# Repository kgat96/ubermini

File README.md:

# ubermini

Project Ubermini is an open source wireless development platform suitable for Bluetooth experimentation. Ubermini ships with a capable BLE (Bluetooth Smart) sniffer and can sniff some data from Basic Rate (BR) Bluetooth Classic connections.

clone [Ubertooth](https://github.com/greatscottgadgets/ubertooth) project

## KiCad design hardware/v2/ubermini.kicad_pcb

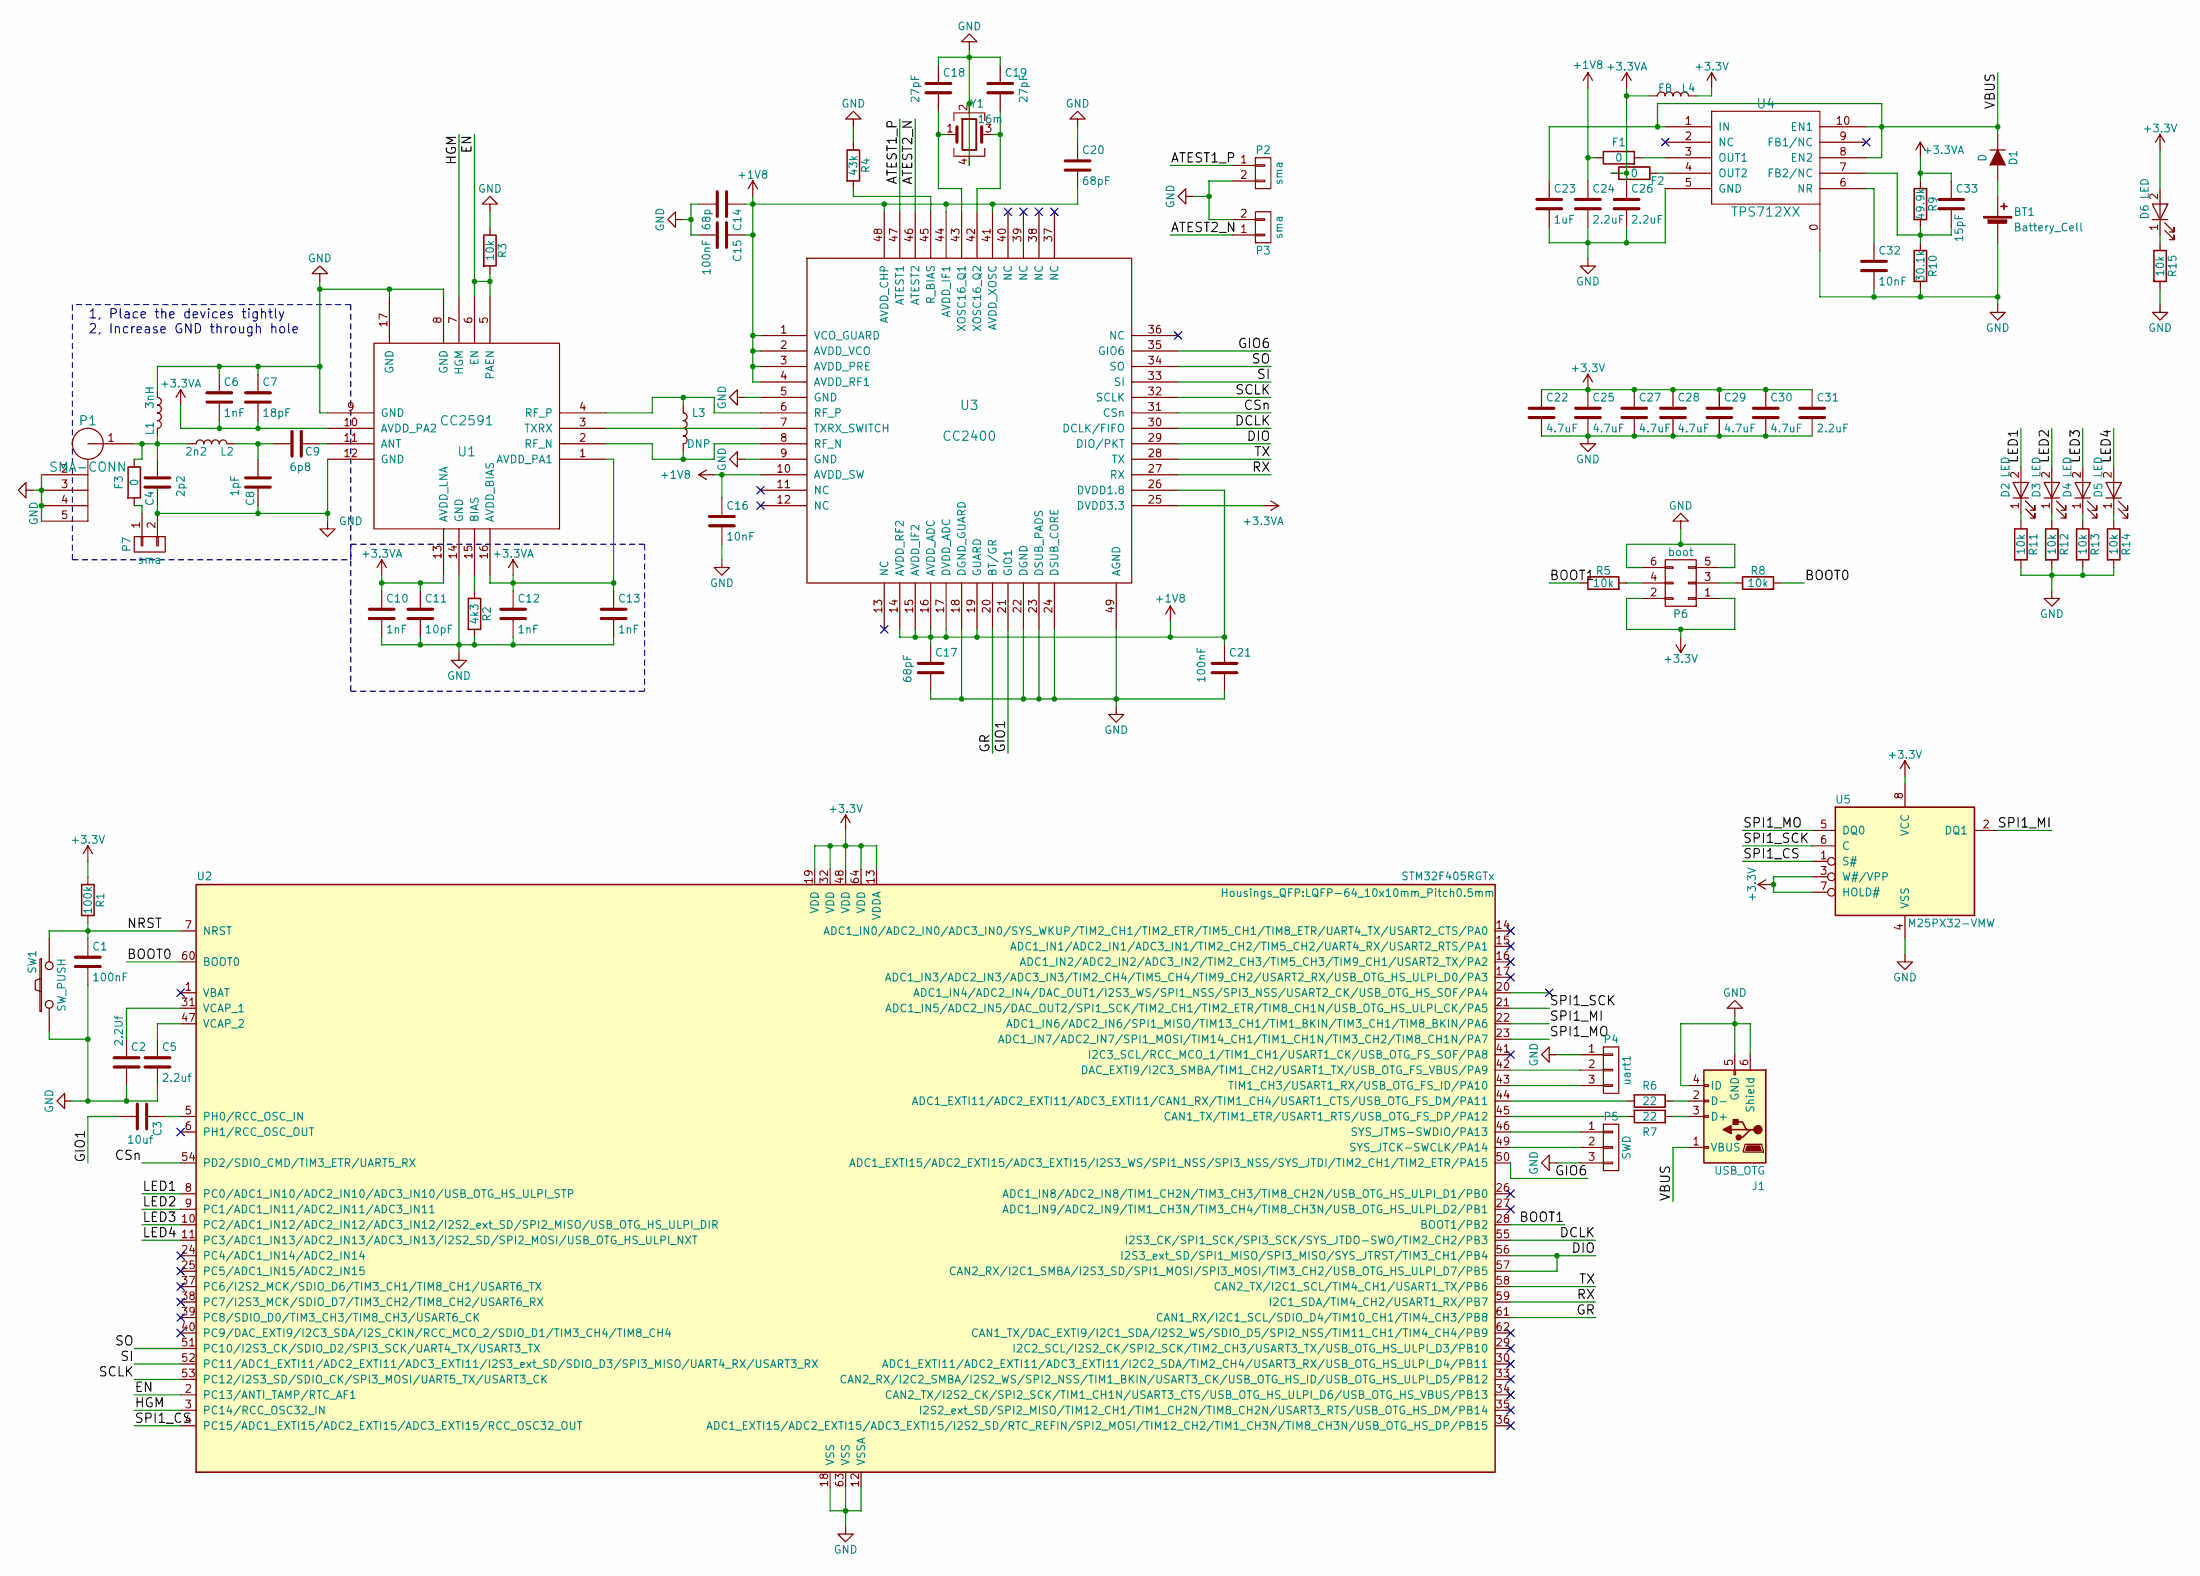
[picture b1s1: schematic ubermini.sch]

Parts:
BT1: Battery_Cell; Pin_Header_Straight_1x02
C1, C15, C21: 100nF; C_0603_HandSoldering
C2: 2.2Uf; C_0603_HandSoldering
C3: 10uf; C_0603_HandSoldering
C4: 2p2; C_0402
C5: 2.2uf; C_0603_HandSoldering
C6, C10, C12, C13: 1nF; C_0603_HandSoldering
C7: 18pF; C_0603_HandSoldering
C8: 1pF; C_0402
C9: 6p8; C_0402
C11: 10pF; C_0603_HandSoldering
C14: 68p; C_0603_HandSoldering
C16, C32: 10nF; C_0603_HandSoldering
C17, C20: 68pF; C_0603_HandSoldering
C18, C19: 27pF; C_0603_HandSoldering
C22, C25, C27, C28, C29, C30: 4.7uF; C_0603_HandSoldering
C23: 1uF; C_0603_HandSoldering
C24, C26, C31: 2.2uF; C_0603_HandSoldering
C33: 15pF; C_0603_HandSoldering
D1: D; R_0805_HandSoldering
D2, D3, D4, D5, D6: LED; LED_0805
F1, F2, F3: 0; C_0201
J1: USB_OTG; USB_Mini-B_s
L1: 3nH; C_0603
L2: 2n2; C_0603
L3: DNP; C_0402
L4: FB; C_0603_HandSoldering
P1: SMA-CONN; sma
P2, P3, P7: sma; U.FL
P4: uart1; Pin_Header_Straight_1x03
P5: SWD; Pin_Header_Straight_1x03
P6: boot; Pin_Header_Straight_2x03
R1: 100k; R_0603_HandSoldering
R2: 4k3; R_0603_HandSoldering
R3, R5, R8, R11, R12, R13, R14, R15: 10k; R_0603_HandSoldering
R4: 43k; R_0603_HandSoldering
R6, R7: 22; R_0603_HandSoldering
R9: 49.9k; R_0603_HandSoldering
R10: 30.1k; R_0603_HandSoldering
SW1: SW_PUSH; SW_SPST_FSMSM
U1: CC2591; cc2591
U2: STM32F405RGTx; LQFP-64_10x10mm_Pitch0.5mm
U3: CC2400; cc2400
U4: TPS712XX; tps712
U5: M25PX32-VMW; winband_spi_flash
Y1: 16m; 3225

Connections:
+1V8: C14.1, C15.1, C16.1, C17.1, C20.2, C21.1, C24.1, F1.1, U3.1 (VCO_GUARD), U3.2 (AVDD_VCO), U3.3 (AVDD_PRE), U3.4 (AVDD_RF1), U3.10 (AVDD_SW), U3.14 (AVDD_RF2), U3.15 (AVDD_IF2), U3.16 (AVDD_ADC), U3.17 (DVDD_ADC), U3.19 (GUARD), U3.26 (DVDD1.8), U3.41 (AVDD_XOSC), U3.44 (AVDD_IF1), U3.48 (AVDD_CHP)
+3.3VA: C6.2, C7.2, C10.1, C11.1, C12.1, C13.1, C26.1, C33.1, F2.1, L4.1, R9.1, U1.1 (AVDD_PA1), U1.10 (AVDD_PA2), U1.13 (AVDD_LNA), U1.16 (AVDD_BIAS), U3.25 (DVDD3.3)
+3V3: C22.1, C25.1, C27.1, C28.1, C29.1, C30.1, C31.1, D6.2 (A), L4.2, P6.1, P6.2, R1.1, U2.13 (VDDA), U2.19 (VDD), U2.32 (VDD), U2.48 (VDD), U2.64 (VDD), U5.3 (W#/VPP), U5.7 (HOLD#), U5.8 (VCC)
/ATEST1_P: P2.1, U3.47 (ATEST1)
/ATEST2_N: P3.1, U3.46 (ATEST2)
/BOOT0: R8.2, U2.60 (BOOT0)
/BOOT1: R5.1, U2.28 (BOOT1/PB2)
/CSn: U2.54 (PD2/SDIO_CMD/TIM3_ETR/UART5_RX), U3.31 (CSn)
/DCLK: U2.55 (I2S3_CK/SPI1_SCK/SPI3_SCK/SYS_JTDO-SWO/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), U3.30 (DCLK/FIFO)
/DIO: U2.56 (I2S3_ext_SD/SPI1_MISO/SPI3_MISO/SYS_JTR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), U2.57 (CAN2_RX/I2C1_SMBA/I2S3_SD/SPI1_MOSI/SPI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), U3.29 (DIO/PKT)
/EN: R3.2, U1.5 (PAEN), U1.6 (EN), U2.2 (PC13/ANTI_TAMP/RTC_AF1)
/GIO1: C3.2, U3.21 (GIO1)
/GIO6: U2.50 (ADC1_EXTI15/ADC2_EXTI15/ADC3_EXTI15/I2S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), U3.35 (GIO6)
/GR: U2.61 (CAN1_RX/I2C1_SCL/SDIO_D4/TIM10_CH1/TIM4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), U3.20 (BT/GR)
/HGM: U1.7 (HGM), U2.3 (PC14/RCC_OSC32_IN)
/LED1: D2.2 (A), U2.8 (PC0/ADC1_IN10/ADC2_IN10/ADC3_IN10/USB_O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)
/LED2: D3.2 (A), U2.9 (PC1/ADC1_IN11/ADC2_IN11/ADC3_IN11)
/LED3: D4.2 (A), U2.10 (PC2/ADC1_IN12/ADC2_IN12/ADC3_IN12/I2S2_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)
/LED4: D5.2 (A), U2.11 (PC3/ADC1_IN13/ADC2_IN13/ADC3_IN13/I2S2_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)
/NRST: C1.1, R1.2, SW1.2, U2.7 (NRST)
/RX: U2.59 (I2C1_SDA/TIM4_CH2/USART1_RX/PB7), U3.27 (RX)
/SCLK: U2.53 (PC12/I2S3_SD/SDIO_CK/SPI3_MOSI/UART5_TX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), U3.32 (SCLK)
/SI: U2.52 (PC11/ADC1_EXTI11/ADC2_EXTI11/ADC3_EXTI1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), U3.33 (SI)
/SO: U2.51 (PC10/I2S3_CK/SDIO_D2/SPI3_SCK/UART4_TX/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), U3.34 (SO)
/SPI1_CS: U2.4 (PC15/ADC1_EXTI15/ADC2_EXTI15/ADC3_EXTI1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), U5.1 (S#)
/SPI1_MI: U2.22 (ADC1_IN6/ADC2_IN6/SPI1_MISO/TIM13_CH1/T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), U5.2 (DQ1)
/SPI1_MO: U2.23 (ADC1_IN7/ADC2_IN7/SPI1_MOSI/TIM14_CH1/T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), U5.5 (DQ0)
/SPI1_SCK: U2.21 (ADC1_IN5/ADC2_IN5/DAC_OUT2/SPI1_SCK/TIM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), U5.6 (C)
/TX: U2.58 (CAN2_TX/I2C1_SCL/TIM4_CH1/USART1_TX/PB6), U3.28 (TX)
/VBUS: C23.1, D1.1 (K), J1.1 (VBUS), U4.1 (IN), U4.8 (EN2), U4.10 (EN1)
GND: BT1.2 (-), C1.2, C2.2, C4.1, C5.2, C6.1, C7.1, C8.1, C10.2, C11.2, C12.2, C13.2, C14.2, C15.2, C16.2, C17.2, C18.1, C19.1, C20.1, C21.2, C22.2, C23.2, C24.2, C25.2, C26.2, C27.2, C28.2, C29.2, C30.2, C31.2, C32.2, J1.4 (ID), J1.5 (GND), J1.6 (Shield), L1.1, P1.2 (GND), P1.3 (GND), P1.4 (GND), P1.5 (GND), P2.2, P3.2, P4.1, P5.3, P6.5, P6.6, P7.2, R2.2, R3.1, R4.1, R10.2, R11.2, R12.2, R13.2, R14.2, R15.2, SW1.1, U1.8 (GND), U1.9 (GND), U1.12 (GND), U1.14 (GND), U1.17 (GND), U2.12 (VSSA), U2.18 (VSS), U2.63 (VSS), U3.5 (GND), U3.9 (GND), U3.18 (DGND_GUARD), U3.22 (DGND), U3.23 (DSUB_PADS), U3.24 (DSUB_CORE), U3.49 (AGND), U4.0, U4.5 (GND), U5.4 (VSS), Y1.2, Y1.4
unnamed: BT1.1 (+), D1.2 (A)
unnamed: C2.1, U2.31 (VCAP_1)
unnamed: C3.1, U2.5 (PH0/RCC_OSC_IN)
unnamed: C4.2, F3.1, L1.2, L2.1, P1.1 (RF)
unnamed: C5.1, U2.47 (VCAP_2)
unnamed: C8.2, C9.2, L2.2
unnamed: C9.1, U1.11 (ANT)
unnamed: C18.2, U3.43 (XOSC16_Q1), Y1.1
unnamed: C19.2, U3.42 (XOSC16_Q2), Y1.3
unnamed: C32.1, U4.6 (NR)
unnamed: C33.2, R9.2, R10.1, U4.7 (FB2/NC)
unnamed: D2.1 (K), R11.1
unnamed: D3.1 (K), R12.1
unnamed: D4.1 (K), R13.1
unnamed: D5.1 (K), R14.1
unnamed: D6.1 (K), R15.1
unnamed: F1.2, U4.3 (OUT1)
unnamed: F2.2, U4.4 (OUT2)
unnamed: F3.2, P7.1
unnamed: J1.2 (D-), R6.1
unnamed: J1.3 (D+), R7.1
unnamed: L3.1, U1.4 (RF_P), U3.6 (RF_P)
unnamed: L3.2, U1.2 (RF_N), U3.8 (RF_N)
unnamed: P4.2, U2.42 (DAC_EXTI9/I2C3_SMBA/TIM1_CH2/USART1_TX/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)
unnamed: P4.3, U2.43 (TIM1_CH3/USART1_RX/USB_OTG_FS_ID/PA10)
unnamed: P5.1, U2.46 (SYS_JTMS-SWDIO/PA13)
unnamed: P5.2, U2.49 (SYS_JTCK-SWCLK/PA14)
unnamed: P6.3, R8.1
unnamed: P6.4, R5.2
unnamed: R2.1, U1.15 (BIAS)
unnamed: R4.2, U3.45 (R_BIAS)
unnamed: R6.2, U2.44 (ADC1_EXTI11/ADC2_EXTI11/ADC3_EXTI11/CAN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)
unnamed: R7.2, U2.45 (CAN1_TX/TIM1_ETR/USART1_RTS/USB_OTG_FS_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)
unnamed: U1.3 (TXRX), U3.7 (TXRX_SWITCH)

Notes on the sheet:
1, Place the devices tightly 2, Increase GND through hole

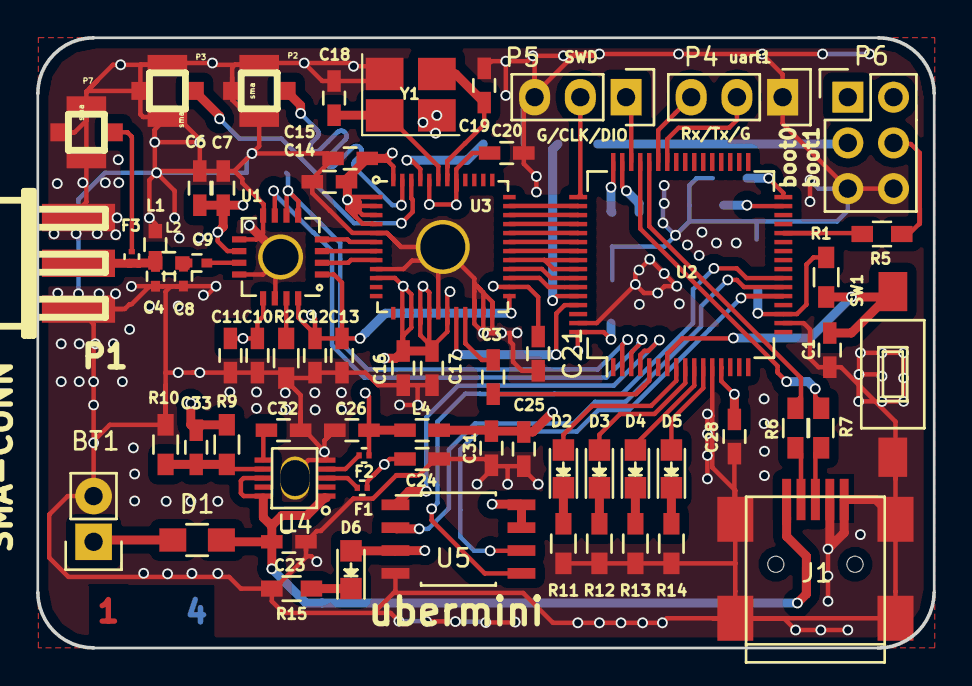
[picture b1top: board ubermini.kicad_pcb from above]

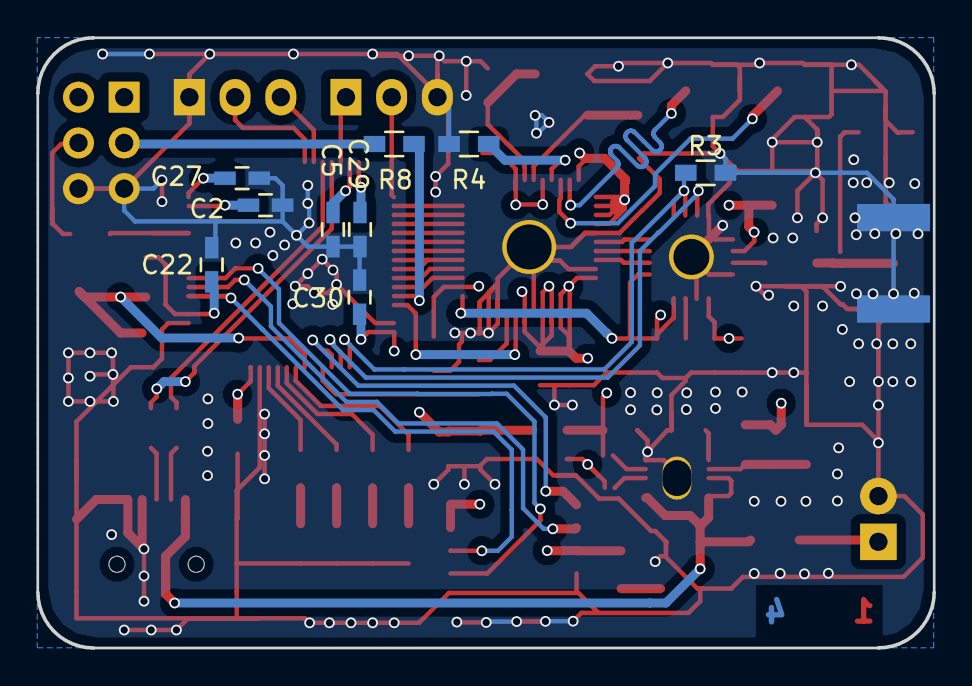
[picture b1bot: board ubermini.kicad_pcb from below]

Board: 4 copper layers, 49.8 x 33.9 mm, 76 parts (9 on the bottom side), 65 nets.

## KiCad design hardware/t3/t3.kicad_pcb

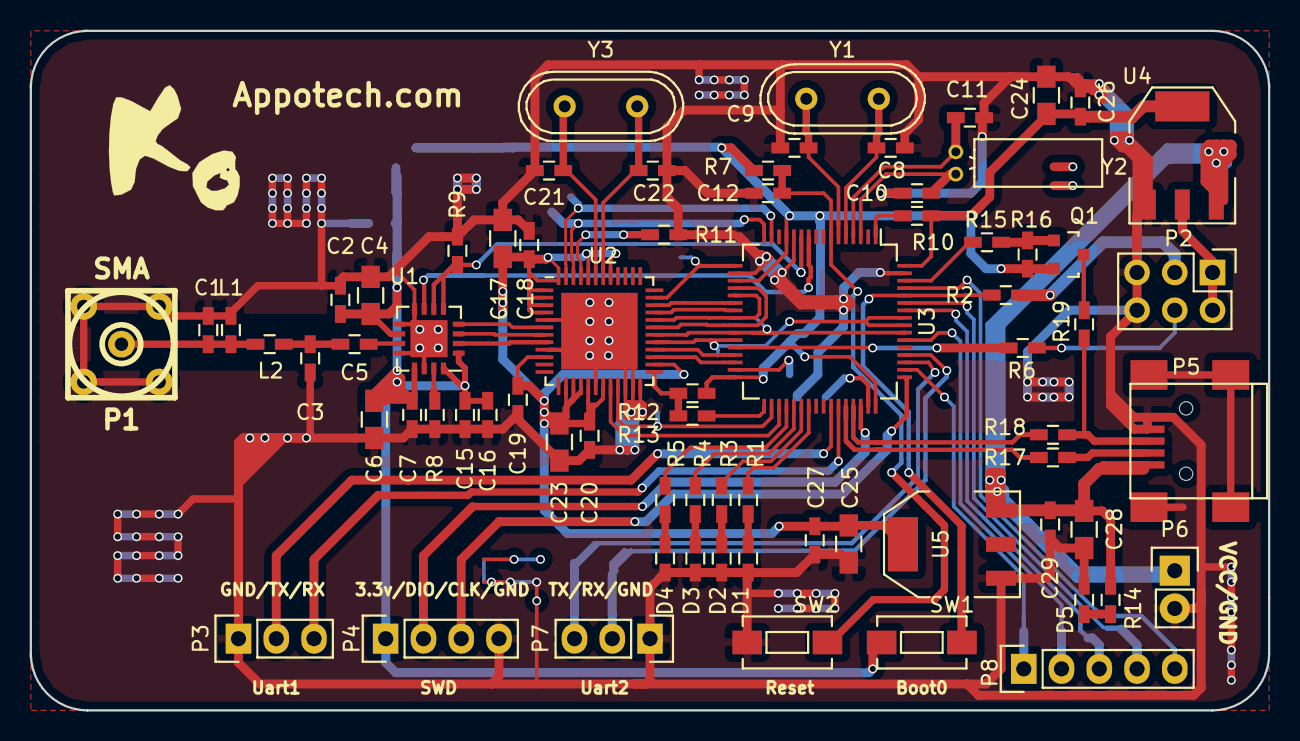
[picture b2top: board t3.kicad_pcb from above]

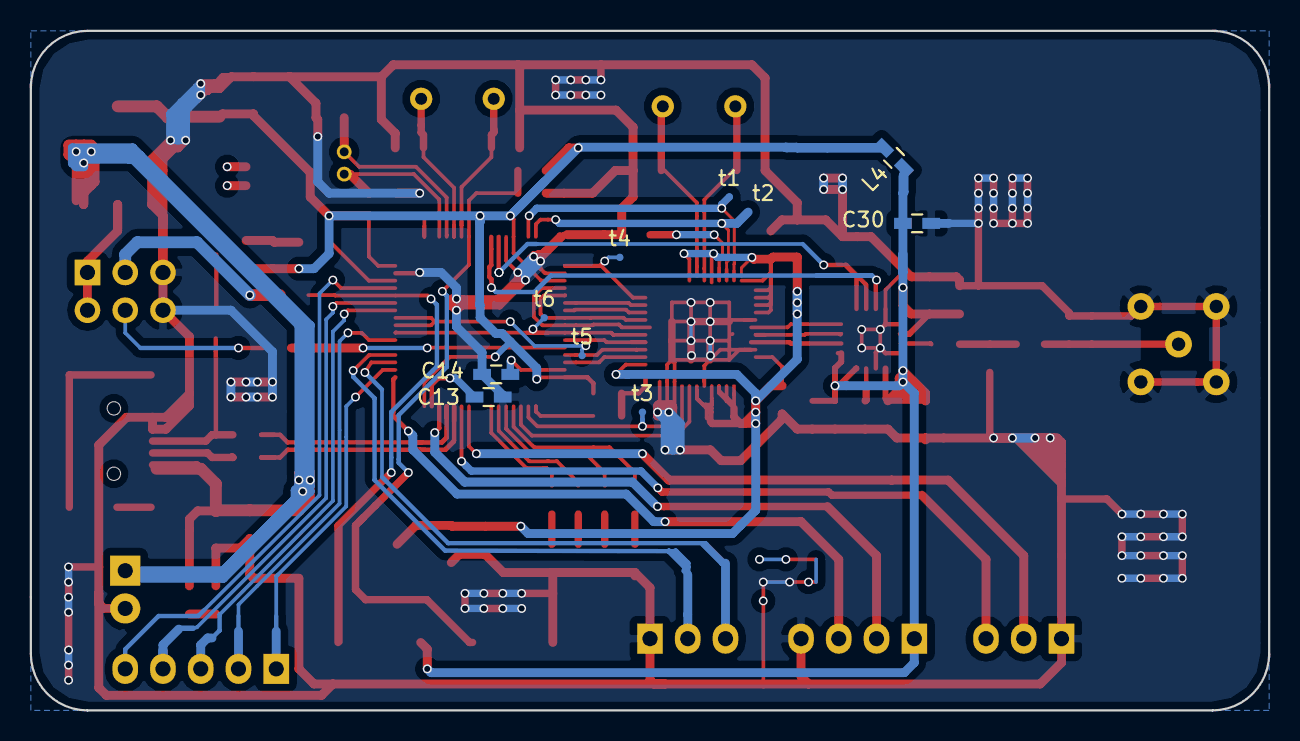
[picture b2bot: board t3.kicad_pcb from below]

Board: 2 copper layers, 83.3 x 45.7 mm, 82 parts (10 on the bottom side), 71 nets.

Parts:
C1: 2p2; C_0603_HandSoldering
C2: 18pf; C_0603_HandSoldering
C3: 1pf; C_0603_HandSoldering
C4, C6: 1nf; C_0805_HandSoldering
C5: 6p8; C_0603_HandSoldering
C7: 10pf; C_0603_HandSoldering
C8, C9: 22pf; C_0603_HandSoldering
C10, C11: 6pf; C_0603_HandSoldering
C12, C26, C27, C29: 100nf; C_0603_HandSoldering
C13, C14: 2.2uf; C_0603_HandSoldering
C15, C16: 1nf; C_0603_HandSoldering
C17, C23: 100nf; C_0805_HandSoldering
C18, C20: 68pf; C_0603_HandSoldering
C19: 10nf; C_0603_HandSoldering
C21, C22: 27pf; C_0603_HandSoldering
C24, C25, C28: 10uf; C_0805_HandSoldering
C30: 2.2pf; C_0603_HandSoldering
D1, D2, D3, D4, D5: LED; C_0603_HandSoldering
L1: 3nH; C_0603_HandSoldering
L2: 2n2; C_0603_HandSoldering
L4: 1Kohms; C_0603_HandSoldering
P1: SMA; lemo_epb00250ntn
P2: CON; Pin_Header_Straight_2x03
P3: UART1; Pin_Header_Straight_1x03
P4: SWD; Pin_Header_Straight_1x04
P5: USB_B; USB_Mini-B
P6: power; Pin_Header_Straight_1x02
P7: UART2; Pin_Header_Straight_1x03
P8: Debug; Pin_Header_Straight_1x05
Q1: 9012; SOT-23
R1, R3, R4, R5, R14: 330; C_0603_HandSoldering
R2, R6: 10K; C_0603_HandSoldering
R7: 100K; C_0603_HandSoldering
R8: 4k3; C_0603_HandSoldering
R9, R16: 10k; C_0603_HandSoldering
R10, R13: 0R; C_0603_HandSoldering
R11: 43k; C_0603_HandSoldering
R12: 0R(NC); C_0603_HandSoldering
R15: 2k2; C_0603_HandSoldering
R17, R18: 22R; C_0603_HandSoldering
R19: 1K5; C_0603_HandSoldering
SW1, SW2: SW_PUSH; SW_SPST_EVQPE1
U1: CC2591; QFN-16-1EP_4x4mm_Pitch0.65mm
U2: CC2400; cc2400_Soldering
U3: STM32F405RGTx; LQFP-64_10x10mm_Pitch0.5mm
U4: LM1117-3.3; SOT-223
U5: LM1117-1.8; SOT-223
Y1, Y3: 16MHz; Crystal_HC49-U_Vertical
Y2: 32.768k; Crystal_Round_Horizontal_3mm
t1, t2, t3, t4, t5, t6: TST; test_pin

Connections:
+1V8: C17.1, C18.1, C19.1, C20.1, C23.1, C25.2, C27.2, U2.1, U2.2, U2.3, U2.4, U2.10, U2.14, U2.15, U2.16, U2.17, U2.19, U2.26, U2.41, U2.44, U2.48, U5.2, U5.4
+3.3VADC: C2.2, C4.2, C6.1, C7.1, C15.1, C16.1, C30.1, L4.1, P4.1, SW1.1, U1.1, U1.10, U1.13, U1.16
+3V3: C24.1, C26.1, L4.2, P2.1, P2.2, Q1.2, R7.1, R10.2, R12.2, R16.2, U3.13, U3.19, U3.32, U3.48, U3.64, U4.2, U4.4
/ATEST1: U2.47, U3.15, t1.1
/ATEST2: U2.46, U3.16, t2.1
/BOOT0: R2.2, SW1.2, U3.60
/BOOT1: R6.1, U3.28
/CSn: U2.31, U3.20, U3.25
/DCLK: U2.30, U3.26, U3.55, t6.1
/DIO: U2.29, U3.27, U3.56, U3.57, t5.1
/GIO1: U2.21, U3.34, t3.1
/GIO6: U2.35, U3.17, t4.1
/GPIO3.3: R13.1, U3.33
/GR: U2.20, U3.35
/HGM: U1.7, U3.10
/LED1: R1.1, U3.39
/LED2: R3.1, U3.38
/LED3: R4.1, U3.37
/LED4: R5.1, U3.36
/NRST: C12.1, R7.2, SW2.2, U3.7
/PAEN: R9.1, U1.5, U1.6, U3.11
/RX: U2.27, U3.30
/SCLK: U2.32, U3.21, U3.24
/SI: U2.33, U3.23
/SO: U2.34, U3.22
/TX: U2.28, U3.29
/UAER1_RX: P3.3, U3.43
/UAER1_TX: P3.2, U3.42
/UAER2_RX: P7.2, U3.52
/UAER2_TX: P7.3, U3.51
/USBEN: R15.2, U3.62
/VBUS: C28.2, C29.2, P5.1, P6.1, R14.1, U4.3, U5.3
/debug1: P8.3, U3.58
/debug2: P8.4, U3.59
/debug3: P8.5, U3.61
/debug4: P8.1, U3.50
/debug5: P8.2, U3.54
GND: C1.1, C2.1, C3.1, C4.1, C6.2, C7.2, C8.2, C9.2, C10.2, C11.2, C12.2, C13.2, C14.2, C15.2, C16.2, C17.2, C18.2, C19.2, C20.2, C21.2, C22.2, C23.2, C24.2, C25.1, C26.2, C27.1, C28.1, C29.1, C30.2, D1.1, D2.1, D3.1, D4.1, D5.1, L1.1, P1.2, P2.5, P2.6, P3.1, P4.4, P5.4, P5.5, P6.2, P7.1, R8.2, R9.2, R11.2, SW2.1, U1.8, U1.9, U1.12, U1.14, U1.17, U2.5, U2.9, U2.18, U2.22, U2.23, U2.24, U2.49, U3.12, U3.18, U3.63, U4.1, U5.1
unnamed: C1.2, L1.2, L2.1, P1.1
unnamed: C3.2, C5.2, L2.2
unnamed: C5.1, U1.11
unnamed: C8.1, U3.5, Y1.2
unnamed: C9.1, U3.6, Y1.1
unnamed: C10.1, U3.3, Y2.2
unnamed: C11.1, U3.4, Y2.1
unnamed: C13.1, U3.31
unnamed: C14.1, U3.47
unnamed: C21.1, U2.43, Y3.1
unnamed: C22.1, U2.42, Y3.2
unnamed: D1.2, R1.2
unnamed: D2.2, R3.2
unnamed: D3.2, R4.2
unnamed: D4.2, R5.2
unnamed: D5.2, R14.2
unnamed: U1.4, U2.6
unnamed: U1.2, U2.8
unnamed: P2.3, R2.1
unnamed: P2.4, R6.2
unnamed: P4.2, U3.46
unnamed: P4.3, U3.49
unnamed: P5.2, R17.2
unnamed: P5.3, R18.2, R19.1
unnamed: Q1.1, R15.1, R16.1
unnamed: Q1.3, R19.2
unnamed: R8.1, U1.15
unnamed: R10.1, U3.1
unnamed: R11.1, U2.45
unnamed: R12.1, R13.2, U2.25
unnamed: R17.1, U3.44
unnamed: R18.1, U3.45
unnamed: U1.3, U2.7

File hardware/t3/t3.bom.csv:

Reference, Value, Footprint, Datasheet

U3,STM32F405RGTx,Housings_QFP:LQFP-64_10x10mm_Pitch0.5mm,
U2,CC2400,Housings_DFN_QFN:QFN-48-1EP_7x7mm_Pitch0.5mm,
U1,CC2591,Housings_DFN_QFN:QFN-16-1EP_4x4mm_Pitch0.65mm,

*U4,LM1117-3.3,TO_SOT_Packages_SMD:SOT-223,
*U5,LM1117-1.8,TO_SOT_Packages_SMD:SOT-223,

*Y1,16MHz,Crystals:Crystal_HC49-U_Vertical,
*Y2,32.768k,Crystals:Crystal_Round_Horizontal_3mm,

*Q1,9012,TO_SOT_Packages_SMD:SOT-23,
*D1,D2,D3,D4,D5,LED,Capacitors_SMD:C_0603_HandSoldering,


*R8,			4.3k,Capacitors_SMD:C_0603_HandSoldering,
*R11,		43k,Capacitors_SMD:C_0603_HandSoldering,
*R17,R18,	22R,Capacitors_SMD:C_0603_HandSoldering,
*R19,		1.5K,Capacitors_SMD:C_0603_HandSoldering,
*R15,		2.2k,Capacitors_SMD:C_0603_HandSoldering,
*R2,R6,R9,R16,		10k,Capacitors_SMD:C_0603_HandSoldering,
*R7,			100K,Capacitors_SMD:C_0603_HandSoldering,
*R1,R3,R4,R5,R14,	330,Capacitors_SMD:C_0603_HandSoldering,

*R10,		0R,Capacitors_SMD:C_0603_HandSoldering,



*C1,C30,  		2.2pf,Capacitors_SMD:C_0603_HandSoldering,
*C14,C13,		2.2uf,Capacitors_SMD:C_0603_HandSoldering,
*C9,C8,			22pf,Capacitors_SMD:C_0603_HandSoldering,
*C2,			18pf,Capacitors_SMD:C_0603_HandSoldering,

*C17,C23,C12,C29,C26,C27,	100nf,Capacitors_SMD:C_0805_HandSoldering,
*C19,			10nf,Capacitors_SMD:C_0603_HandSoldering,
*C3,				1pf,Capacitors_SMD:C_0603_HandSoldering,
*C16,C15,C6,C4,	1nf,Capacitors_SMD:C_0603_HandSoldering,
*C7,				10pf,Capacitors_SMD:C_0603_HandSoldering,

*C5,				6.8pf,Capacitors_SMD:C_0603_HandSoldering,
*C18,C20,		68pf,Capacitors_SMD:C_0603_HandSoldering,
*C21,C22,		27pf,Capacitors_SMD:C_0603_HandSoldering,
*C11,C10,		6pf,Capacitors_SMD:C_0603_HandSoldering,
*C28,C24,C25,	10uf,Capacitors_SMD:C_0805_HandSoldering,

*** Lx,1.5nH, 1nH 0402
*** L2,2.2nH,Capacitors_SMD:C_0603_HandSoldering,
*** L1,3nH,Capacitors_SMD:C_0603_HandSoldering,
*L4,1Kohms,Capacitors_SMD:C_0603_HandSoldering,

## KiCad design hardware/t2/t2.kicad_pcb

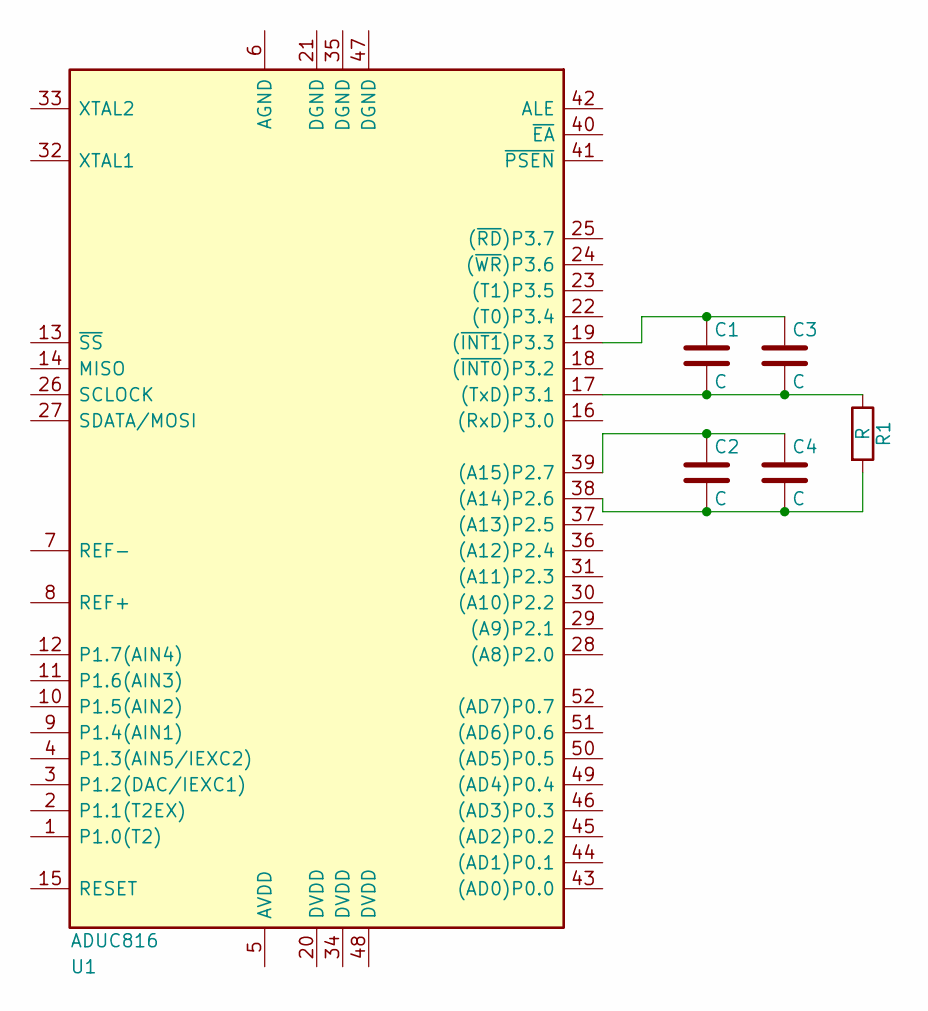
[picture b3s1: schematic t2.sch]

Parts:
C1, C2: C; C_0402
C3, C4: C; C_0603
R1: R; C_0603
U1: ADUC816; LQFP-52_10x10mm_Pitch0.65mm

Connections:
unnamed: C1.1, C3.1, U1.19 ((~INT1~)P3.3)
unnamed: C1.2, C3.2, R1.1, U1.17 ((TxD)P3.1)
unnamed: C2.1, C4.1, U1.39 ((A15)P2.7)
unnamed: C2.2, C4.2, R1.2, U1.38 ((A14)P2.6)

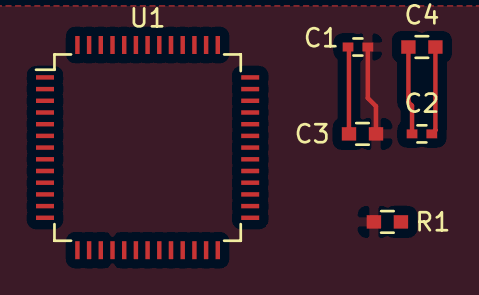
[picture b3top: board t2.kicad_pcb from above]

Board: 2 copper layers, 6 parts (0 on the bottom side), 4 nets.

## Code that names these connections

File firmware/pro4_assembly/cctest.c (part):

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
#define PIN_MOSI    GPIO7       /* Pa.7  */
#define PIN_MISO    GPIO6       /* Pa.6  */
#define PIN_GIO6    GPIO3       /* Pa.3  */

#define PIN_ATEST1  GPIO1       /* Pa.1  */
#define PIN_ATEST2  GPIO2       /* Pa.2  */

#define PIN_CC3V3   GPIO12      /* Pb.12 */
#define PIN_RX      GPIO11      /* Pb.11 */
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#define PIN_USRLED  GPIO8       /* Pc.8  */
#define PIN_RXLED   GPIO7       /* Pc.7  */
#define PIN_TXLED   GPIO6       /* Pc.6  */
#define PIN_CSN     GPIO5       /* Pc.5  */
#define PIN_SCLK    GPIO4       /* Pc.4  */
#define PIN_PAEN    GPIO3       /* Pc.3  */
#define PIN_HGM     GPIO2       /* Pc.2  */

//#define USRLED     (FIO1PIN & PIN_USRLED)
#define USRLED_SET gpio_set(GPIOC, PIN_USRLED)
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#define RX_CLR     gpio_clear(GPIOB, PIN_RX)
#define TX_SET     gpio_set(GPIOB, PIN_TX)
#define TX_CLR     gpio_clear(GPIOB, PIN_TX)
#define CSN_SET    gpio_set(GPIOC, PIN_CSN)
#define CSN_CLR    gpio_clear(GPIOC, PIN_CSN)
#define SCLK_SET   gpio_set(GPIOC, PIN_SCLK)
#define SCLK_CLR   gpio_clear(GPIOC, PIN_SCLK)
#define MOSI_SET   gpio_set(GPIOA, PIN_MOSI)
#define MOSI_CLR   gpio_clear(GPIOA, PIN_MOSI)
//#define GIO6       (FIO2PIN & PIN_GIO6)
#define GIO6_SET   gpio_set(GPIOA, PIN_GIO6)
#define GIO6_CLR   gpio_clear(GPIOA, PIN_GIO6)
#define BTGR_SET   gpio_set(GPIOB, PIN_BTGR)
#define BTGR_CLR   gpio_clear(GPIOB, PIN_BTGR)
#define MISO       gpio_get(GPIOA, PIN_MISO)

#define PAEN     gpio_get(GPIOC, PIN_PAEN)
#define PAEN_SET gpio_set(GPIOC, PIN_PAEN)
#define PAEN_CLR gpio_clear(GPIOC, PIN_PAEN)
#define HGM      gpio_get(GPIOC, PIN_HGM)
#define HGM_SET  gpio_set(GPIOC, PIN_HGM)
#define HGM_CLR  gpio_clear(GPIOC, PIN_HGM)

/* operating modes */
enum operating_modes {
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     * ADC can optionally be configured for ATEST1 and ATEST2, but for now we
     * set them as floating inputs.
     */
    gpio_mode_setup(GPIOA, GPIO_MODE_INPUT, GPIO_PUPD_PULLUP, PIN_ATEST1 | PIN_ATEST2);
}


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#endif

    /* Set GPIO LED. */
    gpio_mode_setup(GPIOC, GPIO_MODE_OUTPUT, GPIO_PUPD_PULLDOWN, GPIO8); // LED1
    gpio_mode_setup(GPIOC, GPIO_MODE_OUTPUT, GPIO_PUPD_PULLDOWN, GPIO7); // LED2
    gpio_mode_setup(GPIOC, GPIO_MODE_OUTPUT, GPIO_PUPD_PULLDOWN, GPIO6); // LED3
    gpio_mode_setup(GPIOB, GPIO_MODE_OUTPUT, GPIO_PUPD_PULLDOWN, GPIO15); // LED4

    /* Setup GPIO pins for USART1 transmit. */
    gpio_mode_setup(GPIOA, GPIO_MODE_AF, GPIO_PUPD_PULLDOWN, GPIO9);
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    gpio_mode_setup(GPIOB, GPIO_MODE_OUTPUT, GPIO_PUPD_PULLUP,
            PIN_TX | PIN_CC3V3 | PIN_RX | PIN_BTGR);
    gpio_mode_setup(GPIOC, GPIO_MODE_OUTPUT, GPIO_PUPD_PULLUP,
            PIN_USRLED | PIN_RXLED | PIN_TXLED | PIN_CSN | PIN_SCLK | PIN_PAEN | PIN_HGM);

    BTGR_CLR; TX_CLR; RX_CLR;

    // set debug gpio 5 PD2
    gpio_mode_setup(GPIOD, GPIO_MODE_INPUT, GPIO_PUPD_PULLUP, GPIO2);
    // set debug gpio 3 PB8
    gpio_mode_setup(GPIOB, GPIO_MODE_INPUT, GPIO_PUPD_PULLUP, GPIO8);
    // set debug gpio 2 PB7
    gpio_mode_setup(GPIOB, GPIO_MODE_INPUT, GPIO_PUPD_PULLUP, GPIO7);
    // set debug gpio 1 PB6
    gpio_mode_setup(GPIOB, GPIO_MODE_INPUT, GPIO_PUPD_PULLUP, GPIO6);

#if 1
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     *
     *       NSS          SCK                   MISO                    MOSI
     *   --------------   -------------------   -------------           ---------------
     * SPI1  PA4, PA15    PA5, PB3              PA6, PB4                PA7, PB5
     * SPI2  PB9, PB12,   PI0                   PB10, PB13, PD3, PI1    PB14, PC2, PI2  PB15, PC3, PI3
     * SPI3  PA15*, PA4*  PB3*, PC10*           PB4*, PC11*             PB5*, PD6, PC12*
     * SPI4  PE4,PE11     PE2, PE12             PE5, PE13               PE6, PE14
     * SPI5  PF6, PH5     PF7, PH6              PF8                     PF9, PF11, PH7
     * SPI6  PG8          PG13                  PG12                    PG14
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     * Pin name with * is alternate function 6 otherwise use alternate function 5.
     *
     * MEMS uses SPI5 - SCK (PF7), MISO (PF8), MOSI (PF9),
     * MEMS CS* (PC1)  -- GPIO
     * MEMS INT1 = PA1, MEMS INT2 = PA2
     */

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    gpio_mode_setup(GPIOB, GPIO_MODE_INPUT, GPIO_PUPD_PULLUP, GPIO0);
    gpio_mode_setup(GPIOB, GPIO_MODE_INPUT, GPIO_PUPD_PULLUP, GPIO1);

    // set debug gpio 4 PA15 to NSS(cs)
    gpio_mode_setup(GPIOA, GPIO_MODE_AF, GPIO_PUPD_PULLUP, GPIO15);
    gpio_set_af(GPIOA, GPIO_AF6, GPIO15);
    // set spi sck PB3
    gpio_mode_setup(GPIOB, GPIO_MODE_AF, GPIO_PUPD_PULLUP, GPIO3);
    gpio_set_af(GPIOB, GPIO_AF6, GPIO3);
    // set spi MISO PB4
    //gpio_mode_setup(GPIOB, GPIO_MODE_AF, GPIO_PUPD_PULLUP, GPIO4);
    //gpio_set_af(GPIOB, GPIO_AF6, GPIO4);
    // set spi MoSI PB5
    gpio_mode_setup(GPIOB, GPIO_MODE_AF, GPIO_PUPD_PULLUP, GPIO5);
    gpio_set_af(GPIOB, GPIO_AF6, GPIO5);

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{
    u32 msb = 1 << (len - 1);

    /* start transaction by dropping CSN */
    CSN_CLR;

    while (len--) {
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
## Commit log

2016-11-08 init repo
2016-11-09 fix[1/x] ubertooth debug board
2016-11-11 fix[2/x] ubertooth debug board
2016-11-11 fix[3/x] ubertooth debug board
2016-11-14 fix[4/x] ubertooth debug board
2016-11-14 fix[5/x] ubertooth debug board
2016-11-15 fix[6/x] ubertooth debug board
2016-11-17 update[7/x] ubertooth debug board
2016-11-21 update[8/x] add logo & fix layout
2016-11-22 firmware: update libopencm3 lib @ win7
2016-11-22 firmware: build blink
2016-11-25 hardware: update gerber file
2016-11-25 push LPC datasheet
2016-11-25 sch: t4
2016-11-30 cctest
2016-12-04 add libbtbb source
2016-12-04 cc init success
2016-12-05 pre3 clock
2016-12-11 pro3: add timr2 100ns clock
2016-12-12 upload pro4_assembly
2016-12-17 pro5 test uart dma
2016-12-18 bt pact rec
2016-12-20 pro6 usb
2016-12-21 pro6 usb use otgfs
2016-12-21 chmod 755/766
2016-12-26 usb poll hci
2016-12-27 pc soft
2017-01-02 pc tools
2017-01-04 spectrum debug led
2017-01-05 usb: add debug info
2017-01-07 pc tool spectrum
2017-01-12 fix two board to debug
2017-01-15 dump raw file
2017-01-16 add libbtbb static lib
2017-01-16 sync decode
2017-01-16 patch host tool
2017-02-20 no use libuber
2017-03-16 update libbt
2017-03-16 pro10 patch 1
2017-03-29 fix print ...
2017-03-29 rename uber
2017-04-08 support uber scan
2017-04-23 hw v2 update
2017-05-07 hw v2 add pcb
2017-05-08 hw patch
2017-05-10 hw update
2017-05-12 hw: add spi flash
2017-05-15 add logo
2017-05-16 fix hw
2017-05-18 create gerber file
2017-05-31 upload pcb n2
2017-06-11 blink hw v2
2017-06-13 v2pro2
2017-06-25 v2pro2 fakeuber
2017-08-05 ble send adv packet
2017-10-12 GFSK test
2017-10-18 create v2pro3 ble
2017-10-19 ble patch 1
2017-10-23 ble patch 2
2017-10-24 ble patch 3
2017-11-26 ble patch 4
2017-12-03 ble patch 5
2017-12-03 ble patch 6
2018-01-03 fix project name
2018-01-07 sync 2018.1.7
2018-01-13 sync 2018.1.13
2018-05-29 sync 2018.5.29
2018-06-03 optimize rev
2018-06-04 sync 6.4
2018-06-13 sync6/14
2018-06-23 sync ..
2018-06-26 whiten test
2018-09-05 modify TX/RX function structure
2018-10-02 fix rx/tx
2019-02-17 adv ind
2019-02-17 v2pro4
2019-03-10 connnnnnn
2019-03-17 fix cc2400 tx problem
2019-05-17 receive ADV connect

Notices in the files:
firmware/pro4_assembly/cctest.c:
Copyright (C) 2016 Kage Shen <kgat96@gmail.com>
This program is free software; you can redistribute it and/or modify
it under the terms of the GNU General Public License version 2 as
published by the Free Software Foundation.
